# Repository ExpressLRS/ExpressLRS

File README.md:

<center>

</center>

**ExpressLRS** is developed and maintained by **ExpressLRS LLC** and its passionate open source community, working together to advance reliable, high-performance radio control technology.

## Support ExpressLRS
You can support ExpressLRS by contributing code, testing new features, sharing your ideas, or helping others get started. We are exceptionally grateful for those who donate their time to our passion.

If you don't have time to lend a hand in that way but still want to have an impact, consider donating. Donations are used for infrastructure costs and to buy test equipment needed to further the project and make it securely accessible. ExpressLRS accepts donations through Open Collective, which provides recognition of donors and transparency on how that support is utilized.

We appreciate all forms of contribution and hope you will join us on Discord!

## Website
For general information on the project please refer to our guides on the [website](https://www.expresslrs.org/), and our [FAQ](https://www.expresslrs.org/faq/)

## About

ExpressLRS is an open source Radio Link for Radio Control applications. Designed to be the best FPV Racing link, it is based on the fantastic Semtech **SX127x**/**SX1280** LoRa hardware combined with an Espressif or STM32 Processor. Using LoRa modulation as well as reduced packet size it achieves best in class range and latency. It achieves this using a highly optimized over-the-air packet structure, giving simultaneous range and latency advantages. It supports both 900 MHz and 2.4 GHz links, each with their own benefits. 900 MHz supports a maximum of 200 Hz packet rate, with higher penetration. 2.4 GHz supports a blistering fast 1000 Hz on [EdgeTX](http://edgetx.org/). With hundreds of different hardware targets from a wide range of hardware manufacturers, the choice of hardware is constantly growing, with different hardware suited to different requirements.

## Configurator
To configure your ExpressLRS hardware, the ExpressLRS Configurator can be used, which is found here:

https://github.com/ExpressLRS/ExpressLRS-Configurator/releases/

## Community
We have both a [Discord Server](https://discord.gg/expresslrs) and [Facebook Group](https://www.facebook.com/groups/636441730280366), which have great support for new users and constant ongoing development discussion

## Features

ExpressLRS has the following features:

- Up to 1000 Hz Packet Rate
- Telemetry (Betaflight Lua Compatibility)
- Wifi Updates
- Bluetooth or WiFi Sim Joystick
- Oled & TFT Displays
- 2.4 GHz, 900 MHz, and Dual-Band RC Link
- SMD Antenna - allows for easier installation into micros
- Supported receiver protocols: CRSF, SBUS, SUMD, HoTT Telemetry, Scorpion Telemetry, SRXL2 (Spektrum/Avian), MAVLink, and PWM
- VTX and VRX Frequency adjustments from the Lua, including SmartAudio and Tramp support
- Bind Phrases - no need for button binding

with many more features on the way!

## Supported Hardware

ExpressLRS currently supports hardware from a wide range of manufacturers. In principle, the targets listed in the [ExpressLRS Configurator](https://github.com/ExpressLRS/ExpressLRS-Configurator/releases/) are tested and supported hardware.

See [Hardware Selection](https://www.expresslrs.org/hardware/hardware-selection/) for guidance. We do not manufacture any of our hardware, so we can only provide limited support for faulty hardware.

## Developers

If you are a developer and would like to contribute to the project, feel free to join the [discord](https://discord.gg/expresslrs) and chat about bugs and issues. You can also look for issues at the [GitHub Issue Tracker](https://github.com/ExpressLRS/ExpressLRS/issues). The best thing to do is to submit a Pull Request to the GitHub Repository.

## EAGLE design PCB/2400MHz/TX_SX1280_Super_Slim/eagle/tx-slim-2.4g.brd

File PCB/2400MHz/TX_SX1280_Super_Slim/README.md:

# 2.4GHz Slim Tx

This is basically the same PCB as the DIY 2.4GHz JR module but in a smaller form factor. The PCB works in both the slim enclosure and the JR enclosure.

For info on the prebuilt versions, go to the wiki page for [Nuclear Super Slim TX](https://github.com/ExpressLRS/ExpressLRS/wiki/Nuclear-Super-Slim-TX).

### PCB manufacturing

Upload the Gerber file to https://jlcpcb.com/RAT.  Check the price for 5, 10, and 30 pieces.  It is sometimes cheaper to order 30 than 10 and only a minor increase in price compared to 5.

*PCB Thickness: 1mm*
*Remove Order Number: Specify a location*

### BOM

- E28-2G4M27S SX1280 Wireless module 2.4G 27dBm https://www.aliexpress.com/item/33004335921.html
- 3.3V DC-DC Step Down Power Supply https://www.aliexpress.com/item/32880983608.html
- 10k 0402 resistor https://www.aliexpress.com/item/4000049692396.html
- SMA or RPSMA pigtail https://www.aliexpress.com/item/4000848776660.html https://www.aliexpress.com/item/4000848776660.html
- WROOM32 module https://www.aliexpress.com/item/ESP32-ESP-32S-WIFI-Bluetooth-Module-240MHz-Dual-Core-CPU-MCU-Wireless-Network-Board-ESP-WROOM/4000230070560.html
- 10uF 3528 Cap https://www.aliexpress.com/item/32666405364.html?algo_pvid=365ae59d-9e6c-46b7-9792-2656b0961f70&algo_expid=365ae59d-9e6c-46b7-9792-2656b0961f70-6&btsid=0bb0623116027669252885518ea610&ws_ab_test=searchweb0_0,searchweb201602_,searchweb201603_
- 8 Way header https://www.aliexpress.com/item/3pcs-1X40PIN-2-54MM-1x40-Pin-2-54-Round-Female-Pin-Header-connector/32847506950.html?spm=a2g0s.9042311.0.0.27424c4dOfOrhZ
- 4 M3 screws 4-7mm (use leftover motor/frame screws)
- 2.4GHz antenna
- A few wires
- 3D printed case

### Build order

Click this image to watch a video of the building of an older version of this module

0. Print both STLs in the orientation shown in the image below, use light support (15%)
1. Move 0 ohm resistor on E28 to make it use the external antenna
2. Cut trace on voltage regulator and solder 3.3V bridge (see image)
3. Solder ESP32 and E28 to PCB
4. Solder capacitor with stripe closer to the ESP32
5. Solder 10k resistor
6. Bridge the boot pads near the E28
7. Solder 4 pin header to ESP32 side of PCB
8. Put voltage regulator on the pin header UPSIDE DOWN and solder
9. Clip extra length of header pins
10. Connect serial adapter to with the 6 pins (SET POWER TO 3.3V OR YOU WILL KILL THE ESP!)
11. Upload your build (if it doesn't work, check for shorts, add flux and heat to solder joints)
12. Solder wires to G, +, S on E28 side of board (If they're on the ESP side they might get in the way of the board fitting all the way inside the enclosure)
13. Insert antenna pigtail
14. Insert header to back of enclosure (I don't have the correct header so I had to trim mine a bit)
15. Solder wires to the three pins on the right +, G, S from left to right
16. Insert PCB and attach antenna pigtail
17. Connect to handset and verify voltage from regulator is 3.3V
18. Bridge vreg en pads
19. Screw down cover
20. Make sure LUA script can communicate with module

### STLs

[Slim enclosure onshape link](https://cad.onshape.com/documents/2cffc645d8696d047935ac89/w/6acaaaa832f4b23c1c8ac47e/e/49ad20ba4b7d79ea1d683a18)
[JR enclosure onshape link](https://cad.onshape.com/documents/50ada7dd7257b3b4cfa71d02/w/741afccb437d7d488507c71b/e/4760c734ca4584832616ed85)

### Pics

### Schematic and PCB layout

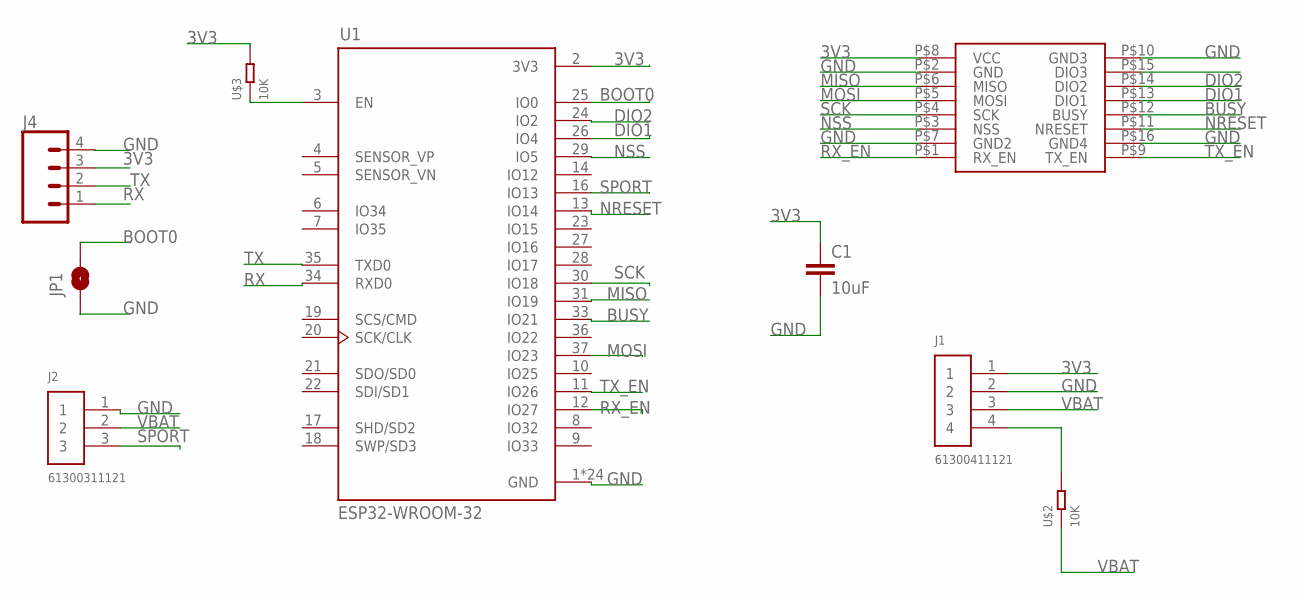
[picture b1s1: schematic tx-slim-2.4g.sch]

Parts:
C1: 10uF; 1210
J1: 61300411121
J2: 61300311121
J4: CONN_04SMD_RA_FEMALE; 1X04_SMD_RA_FEMALE
JP1: JUMPER-SMT_2_NO_NO-SILK; SMT-JUMPER_2_NO_NO-SILK
U1: ESP32-WROOM-32; MODULE_ESP32-WROOM-32
U$1: E28
U$2, U$3: 10K; R0805

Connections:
3V3: C1.1, J1.1, J4.3, U1.2 (3V3), U$1.P$8 (VCC), U$3.2
BOOT0: JP1.2, U1.25 (IO0)
BUSY: U1.33 (IO21), U$1.P$12 (BUSY)
DIO1: U1.26 (IO4), U$1.P$13 (DIO1)
DIO2: U1.24 (IO2), U$1.P$14 (DIO2)
GND: C1.2, J1.2, J2.1, J4.4, JP1.1, U1.1 (GND), U1.15 (GND), U1.38 (GND), U1.39_1 (GND), U1.39_2 (GND), U1.39_3 (GND), U1.39_4 (GND), U1.39_5 (GND), U1.39_6 (GND), U1.39_7 (GND), U1.39_8 (GND), U1.39_9 (GND), U1.39_10 (GND), U1.39_11 (GND), U1.39_12 (GND), U1.39_13 (GND), U1.39_14 (GND), U1.39_15 (GND), U1.39_16 (GND), U1.39_17 (GND), U1.39_18 (GND), U1.39_19 (GND), U1.39_20 (GND), U1.39_21 (GND), U$1.P$2 (GND), U$1.P$7 (GND2), U$1.P$10 (GND3), U$1.P$16 (GND4)
MISO: U1.31 (IO19), U$1.P$6 (MISO)
MOSI: U1.37 (IO23), U$1.P$5 (MOSI)
unnamed: J1.4, U$2.2
unnamed: U1.3 (EN), U$3.1
NRESET: U1.13 (IO14), U$1.P$11 (NRESET)
NSS: U1.29 (IO5), U$1.P$3 (NSS)
RX: J4.1, U1.34 (RXD0)
RX_EN: U1.12 (IO27), U$1.P$1 (RX_EN)
SCK: U1.30 (IO18), U$1.P$4 (SCK)
SPORT: J2.3, U1.16 (IO13)
TX: J4.2, U1.35 (TXD0)
TX_EN: U1.11 (IO26), U$1.P$9 (TX_EN)
VBAT: J1.3, J2.2, U$2.1

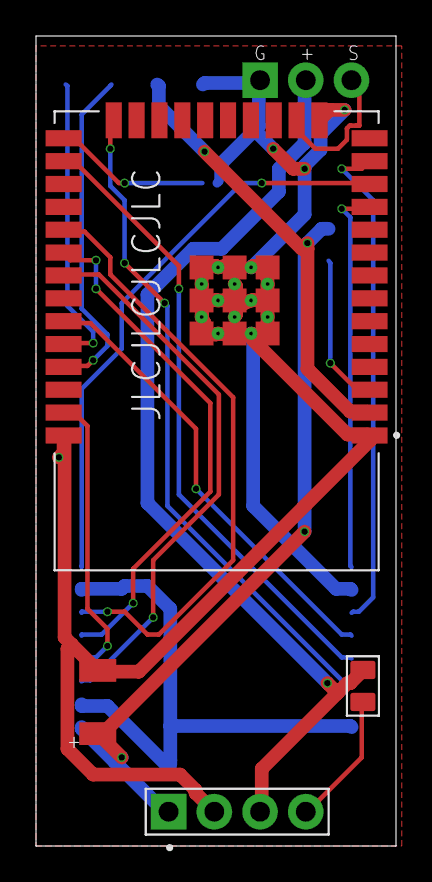
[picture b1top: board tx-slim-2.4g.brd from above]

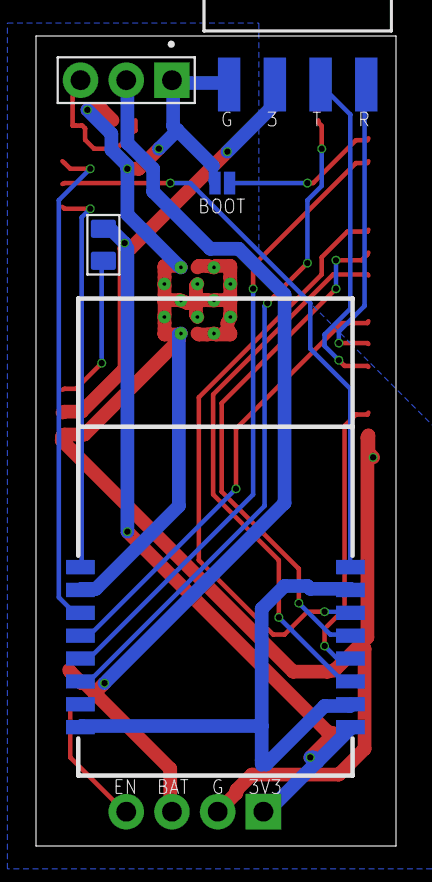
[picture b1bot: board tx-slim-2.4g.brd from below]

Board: 2 copper layers, 20.0 x 45.0 mm, 9 parts (5 on the bottom side), 19 nets.

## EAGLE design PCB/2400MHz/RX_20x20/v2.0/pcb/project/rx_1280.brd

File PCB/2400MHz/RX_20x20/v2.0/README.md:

# 20x20 2.4G RX PCB

### PCB manufacturing

Upload the Gerber file to https://jlcpcb.com/RAT.  Check the price for 5, 10, and 30 pieces.  It is sometimes cheaper to order 30 than 10 and only a minor increase in price compared to 5.

*PCB Thickness: 1mm*

### BOM

- SX1280 Wireless module 2.4G https://www.aliexpress.com/item/32946774361.html
- AMS1117 3.3 Power Reg https://www.aliexpress.com/item/32910803907.html
- ESP-01F https://www.aliexpress.com/item/32921798906.html
- C1 3528 10uF Tantalum Capacitor
- C2 3528 47uF Tantalum Capacitor
- R1 0805 10K Resistor
- R2 0805 10K Resistor
- R3 0805 330R Resistor
- R4 0805 270R Resistor
- 0603 LED
- u.fl connector https://www.aliexpress.com/item/33059352910.html
- Button https://www.ebay.com.au/itm/10pcs-3-6-2-5mm-Tactile-Push-Button-Switch-Tact-Switch-Micro-Switch-2-Pin-SMD/282930653324?hash=item41dffb288c:g:IEoAAOSwyi1a19WD

### Build order

- Solder the ESP-01F module.
- Solder C1 and C2
- Solder the reg
- Solder the 10K resistors
- Flip the PCB and solder the ground pad under the ESP from the other side
- Solder the SX1280
- Solder R4 and the LED
- Solder the u.fl and button
- Bridge the solder jumper centre pin to either 3v3 (if you have a TCXO 1280 module), or GND (if you have a non-TCXO 1280 module)

### Schematic and PCB layout

### Flashing 

- Connect an FTDI to the GND, 5v, TX and RX pins on the header, then hold the boot button while powering up, and flash the DIY_2400_RX_ESP8285_SX1280_via_UART build in pio

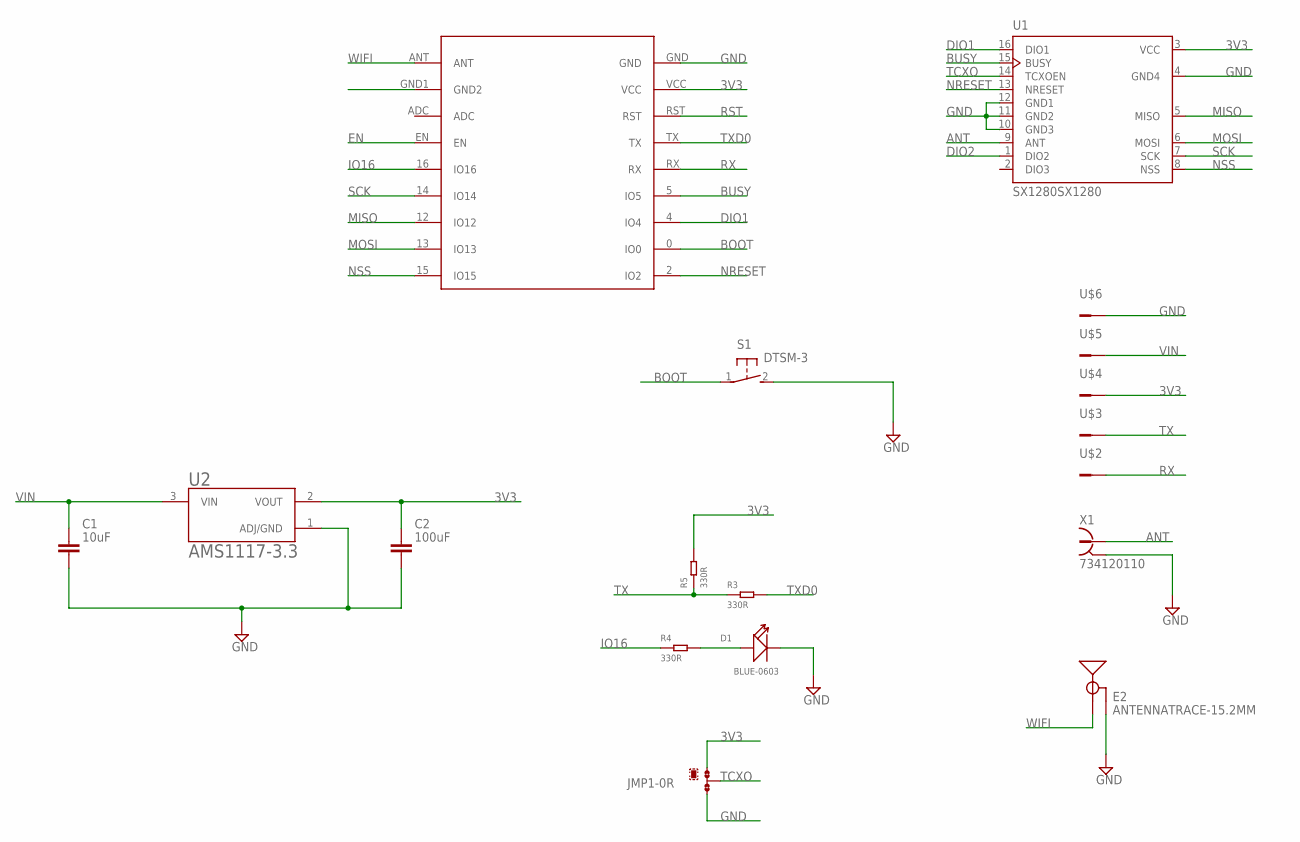
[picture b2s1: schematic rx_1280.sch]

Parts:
C1: 10uF; CAPM3528X210
C2: 100uF; CAPM3528X210
D1: BLUE-0603; LED-0603
E2: ANTENNATRACE-15.2MM; TRACE_ANTENNA_2.4GHZ_15.2MM
JMP1: 0R-JUMPA; A0R-JMP
R3, R4, R5: 330R; R0805
S1: DTSM-3
U1: SX1280SX1280; SX1280
U2: AMS1117-3.3; SOT229P700X180-4N
U$1: ESP-M2
U$2, U$3, U$4, U$5, U$6: CONN-1; PAD1
X1: 734120110

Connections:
3V3: C2.1, JMP1.1, R5.2, U1.3 (VCC), U2.2 (VOUT), U$1.VCC, U$4.P$1
ANT: U1.9 (ANT), X1.1
BOOT: S1.1, U$1.0 (IO0)
BUSY: U1.15 (BUSY), U$1.5 (IO5)
DIO1: U1.16 (DIO1), U$1.4 (IO4)
DIO2: U1.1 (DIO2)
EN: U$1.EN
GND: C1.2, C2.2, D1.-, E2.GND, JMP1.3, S1.2, U1.4 (GND4), U1.10 (GND3), U1.11 (GND2), U1.12 (GND1), U2.1 (ADJ/GND), U$1.GND, U$1.GND1 (GND2), U$6.P$1, X1.S@1 (2), X1.S@2 (2), X1.S@3 (2)
IO16: R4.1, U$1.16 (IO16)
MISO: U1.5 (MISO), U$1.12 (IO12)
MOSI: U1.6 (MOSI), U$1.13 (IO13)
unnamed: D1.+, R4.2
NRESET: U1.13 (NRESET), U$1.2 (IO2)
NSS: U1.8 (NSS), U$1.15 (IO15)
RST: U$1.RST
RX: U$1.RX, U$2.P$1
SCK: U1.7 (SCK), U$1.14 (IO14)
TCXO: JMP1.2, U1.14 (TCXOEN)
TX: R3.1, R5.1, U$3.P$1
TXD0: R3.2, U$1.TX
VIN: C1.1, U2.3 (VIN), U$5.P$1
WIFI: E2.ANT (SIGNAL), U$1.ANT

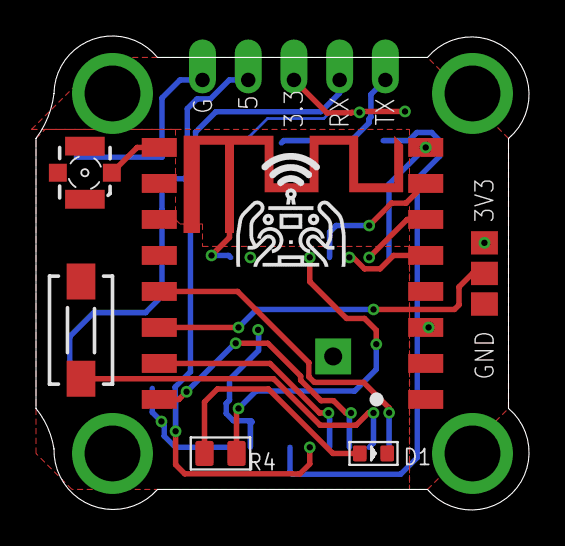
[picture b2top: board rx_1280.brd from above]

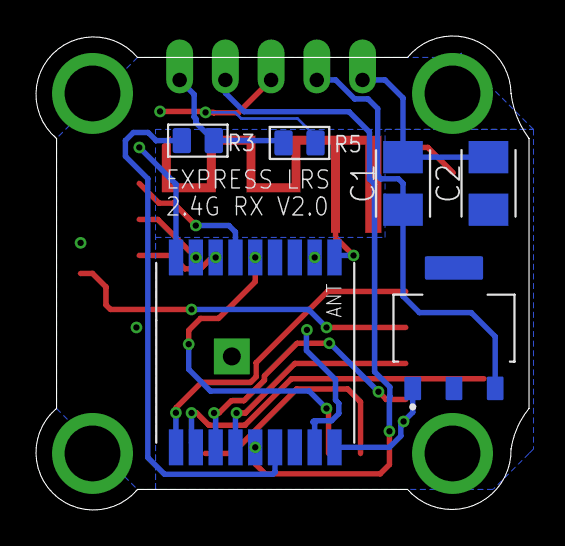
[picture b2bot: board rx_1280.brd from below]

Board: 2 copper layers, 27.4 x 26.3 mm, 18 parts (6 on the bottom side), 19 nets.

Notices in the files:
parts and their libraries:
SparkFun-Capacitors: Licensing: Creative Commons ShareAlike 4.0 International - https://creativecommons.org/licenses/by-sa/4.0
